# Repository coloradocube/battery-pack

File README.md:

# battery-pack
Battery-pack board for 18650 Li ion batteries

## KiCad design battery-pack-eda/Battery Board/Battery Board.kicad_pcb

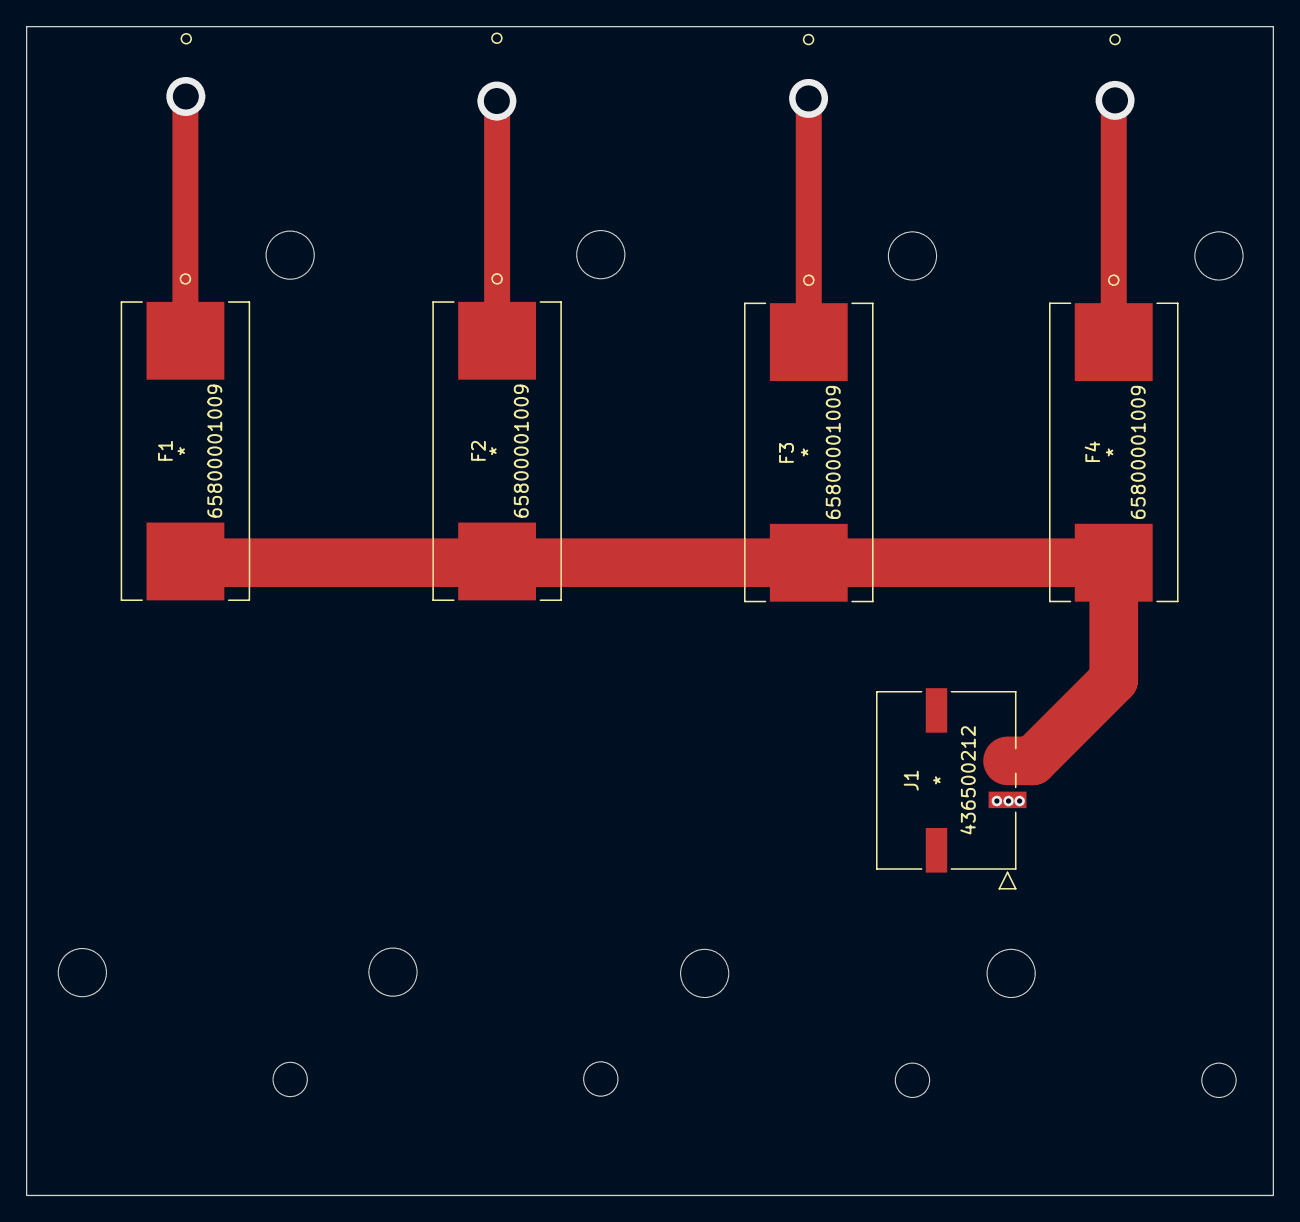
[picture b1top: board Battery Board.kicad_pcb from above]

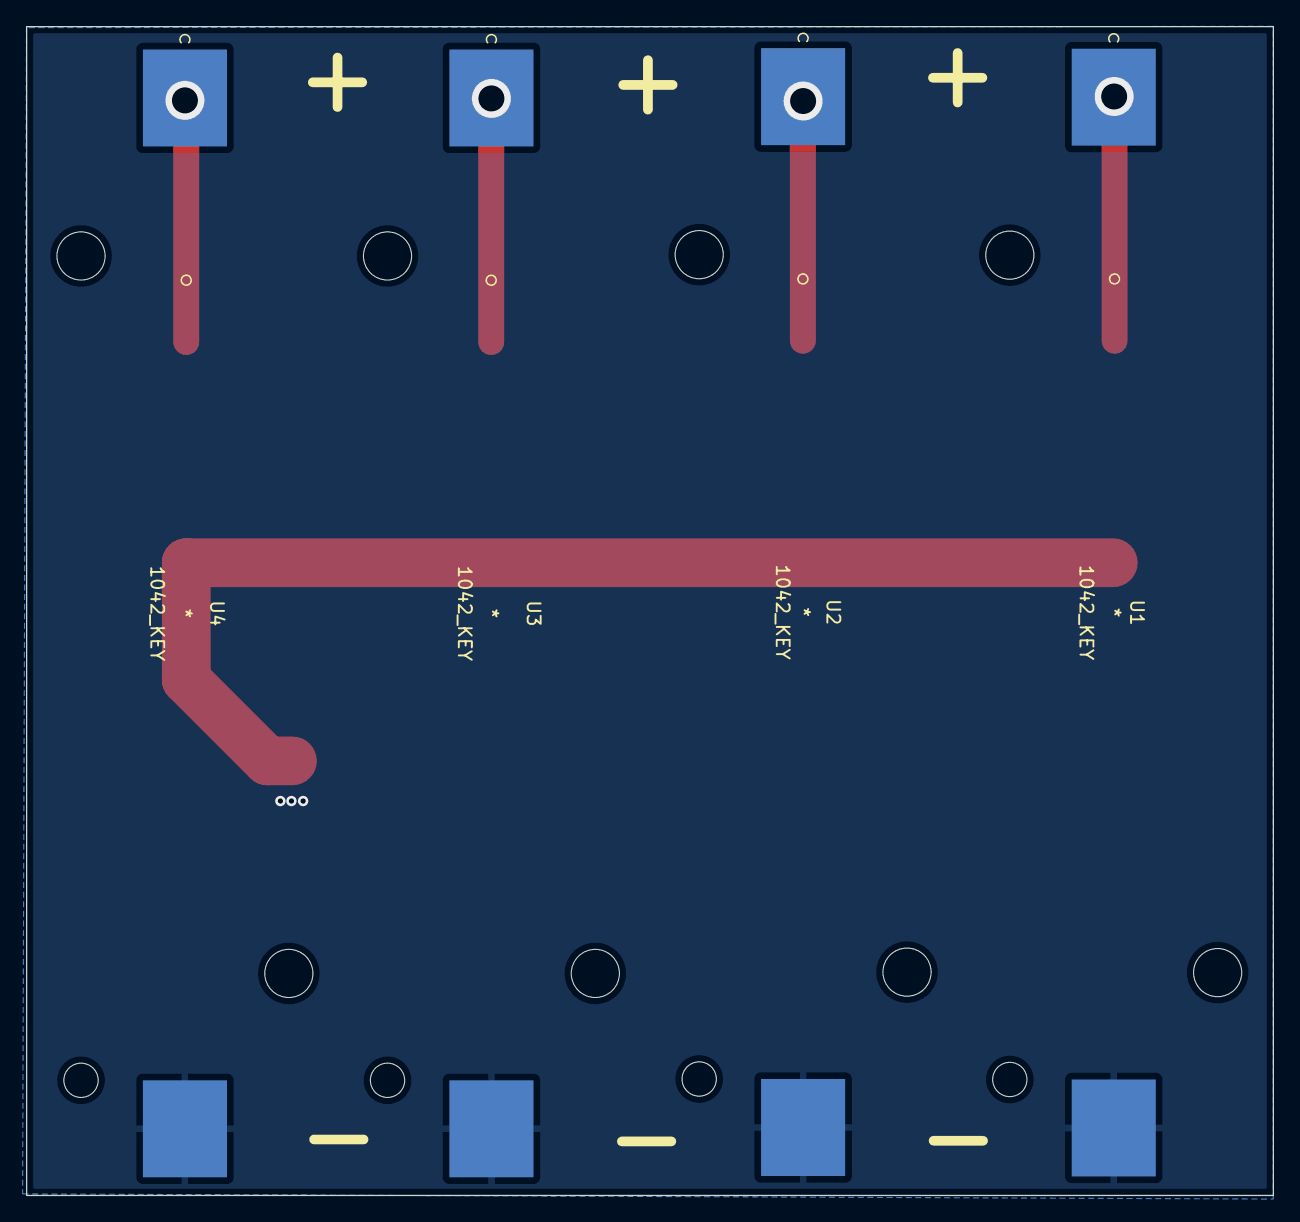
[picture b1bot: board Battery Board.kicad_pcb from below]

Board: 2 copper layers, 96.0 x 90.0 mm, 9 parts (4 on the bottom side), 6 nets.

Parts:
F1, F2, F3, F4: 65800001009
J1: 436500212
U1, U2, U3, U4: 1042_KEY; 1042

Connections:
GND: J1.1, U1.2, U2.2, U3.2, U4.2
unnamed: F1.1, U1.1
unnamed: F1.2, F2.2, F3.2, F4.2, J1.2
unnamed: F2.1, U2.1
unnamed: F3.1, U3.1
unnamed: F4.1, U4.1

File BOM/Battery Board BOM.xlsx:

Part | Manufactorer | Part Number | Quantity | Distributer
Fuse holder | LittleFuse | 65800001009 | 4 | jlpcb
On board connector | Molex | 436500212 | 2 | jlpcb
Battery holder | Keystone | 1042 | 4 | Digi Key

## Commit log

2022-04-21 first separate battery pack commit
2022-04-22 Revision 0.2
2022-04-22 Removed old CAD files
2022-04-24 Added BOM

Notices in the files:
parts and their libraries:
Copyright 2021 Accelerated Designs. All rights reserved.
